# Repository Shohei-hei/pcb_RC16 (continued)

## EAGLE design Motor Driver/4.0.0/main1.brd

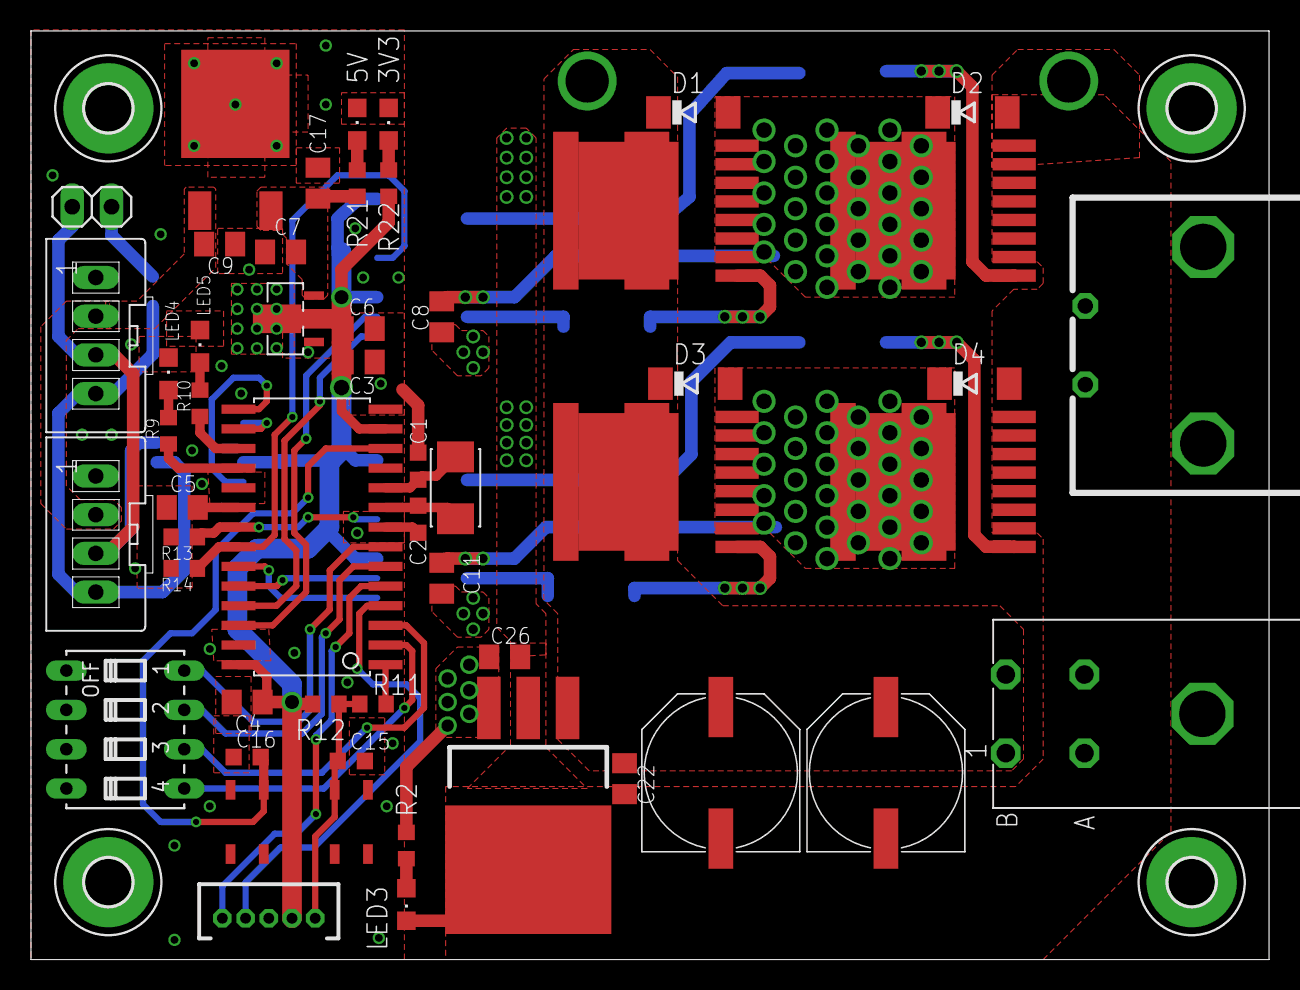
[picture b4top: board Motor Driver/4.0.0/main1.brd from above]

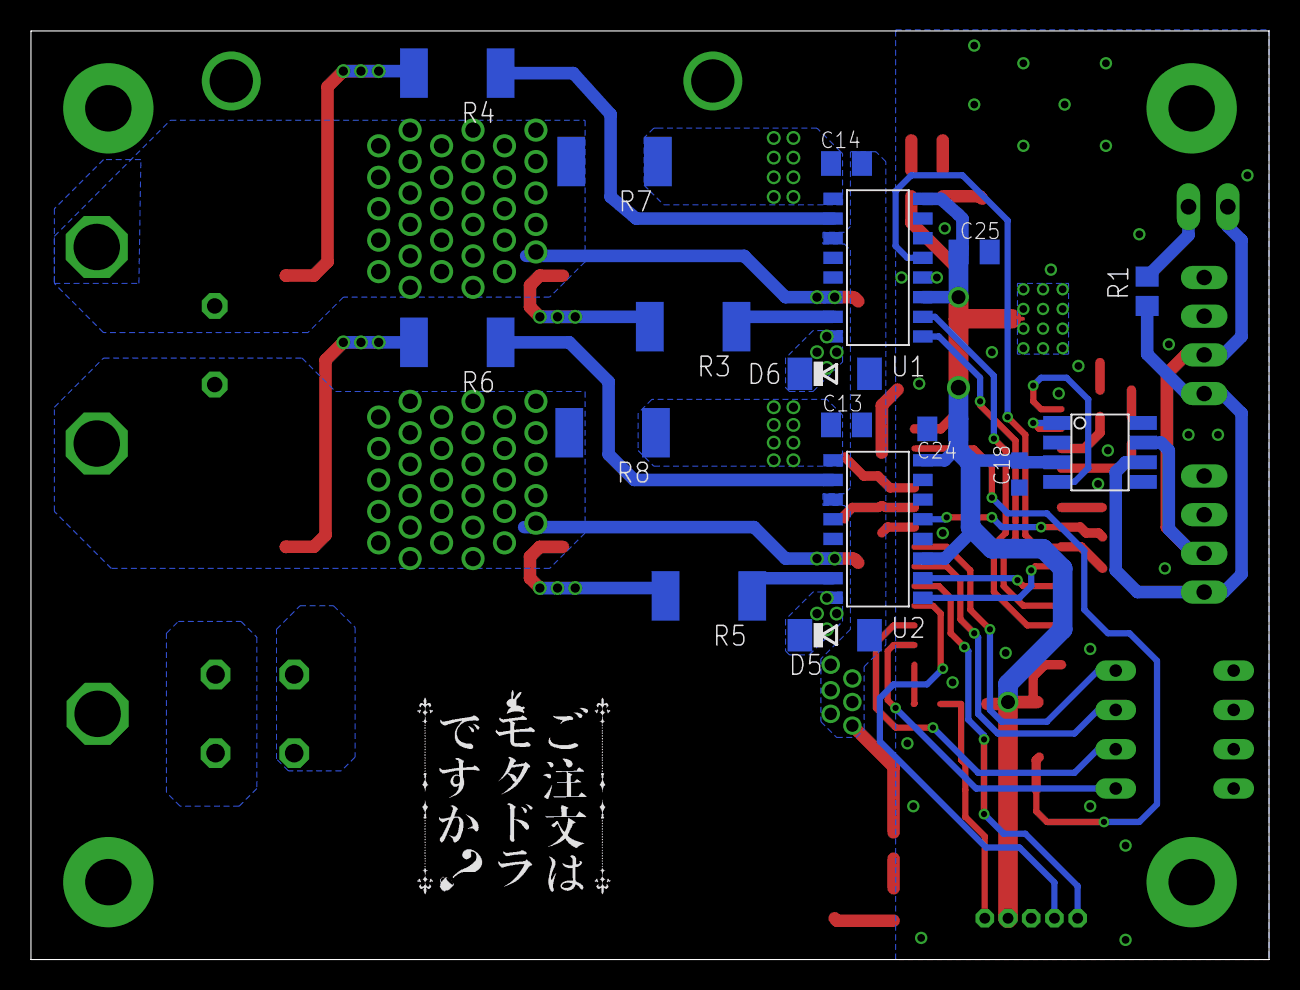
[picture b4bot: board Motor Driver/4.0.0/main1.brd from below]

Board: 2 copper layers, 80.0 x 60.0 mm, 75 parts (18 on the bottom side), 49 nets.

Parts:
3V3, 5V: CHIPLED_0805
C1, C2: 22p; C0603K
C3, C4, C13, C14, C24, C25: 0.1u; C0805K
C5, C6, C7, C8, C9, C11, C17, C22, C26: 4.7u; C0805K
C12, C21: PANASONIC_G
C15, C16, C18: 0.1u; C0603K
CN2, CN3: XA04-T; XA04
D1, D2, D3, D4: SBD; SOD106-R
D5, D6: SOD106-R
H5, H6, H7, H8: MOUNT-PAD-ROUND3.0; 3,0-PAD
IC1: DSPIC33FJ32MC302/64MC202/64MC802/128MC202/128MC802; SOIC28
IC2: REGULATERNJM2845DL1; TO-252-2
IC4: REGULATERAZ1117CR; SOT89
JP3: 1X02
LED3, LED4, LED5: CHIPLED_0805
MC7812BDTRKGOSCT-ND1: REGULATERMIC2940A-5.0WU; TO-263-3
Q2: CRYSTALNX5032GA; NX5032GA
R1: 120; R0805
R2, R12: 1k; R0603
R3, R4, R5, R6: 33; R2512
R7, R8: 470; R2512
R9, R10, R13, R14, R21, R22: 510; R0603
R11: 330; R0603
S2: DIP04S
SW1, SW2: SWITCH_4PALPS; SKRP
U1, U2: SOIC16_N
U$1: CN-D3500D04; D-3500D04
U$2, U$3, U$4, U$5: FET_NCHFDBL0065N40; MO-299A
U$6: MAX3051; SOIC8
U$7: WRITE_FOR_PICT; ZH05
U$8: LOGOGOCHIUSA-14MM; LOGO006
U$9: CN-D3200S02; D-3200S02-S

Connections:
0V: C12.-, C13.2, C14.2, C21.-, C22.2, C26.2, D2.A, D4.A, LED3.C, MC7812BDTRKGOSCT-ND1.2, MC7812BDTRKGOSCT-ND1.4, R7.1, R8.1, U1.P$9, U2.P$9, U$1.01A, U$1.02A, U$3.2, U$3.3, U$3.4, U$3.5, U$3.6, U$3.7, U$3.8, U$5.2, U$5.3, U$5.4, U$5.5, U$5.6, U$5.7, U$5.8
3.3V: C3.1, C4.1, C6.2, C18.2, C24.1, C25.1, IC1.13, IC1.28, IC4.2, IC4.P, R12.2, R22.1, U1.P$3, U1.P$8, U2.P$3, U2.P$8, U$6.3, U$7.2
+5V: C7.2, C17.2, IC2.3, IC4.3, R21.1
+10V: C9.2, CN2.PIN2, CN3.PIN2, IC2.1
BOOTA: C8.1, D6.C, U1.P$16
BOOTB: C11.1, D5.C, U2.P$16
CANH: CN2.PIN3, CN3.PIN3, JP3.2, U$6.7
CANL: CN2.PIN4, CN3.PIN4, R1.1, U$6.6
CRXD: IC1.15, U$6.4
CTXD: IC1.16, U$6.1
DGND: 3V3.C, 5V.C, C1.1, C2.1, C3.2, C4.2, C5.2, C6.1, C7.1, C9.1, C15.2, C16.1, C17.1, C18.1, C24.2, C25.2, CN2.PIN1, CN3.PIN1, IC1.8, IC1.19, IC1.27, IC2.2, IC4.1, LED4.C, LED5.C, R13.2, R14.2, S2.1, S2.2, S2.3, S2.4, SW1.1, SW1.2, SW2.3, SW2.4, U1.P$4, U2.P$4, U$6.2, U$6.5, U$6.8, U$7.3
DIS_A: IC1.22, R14.1, U1.P$5
DIS_B: IC1.21, R13.1, U2.P$5
HA: R3.1, U1.P$15
HB: R5.1, U2.P$15
LA: R4.1, U1.P$10
LB: R6.1, U2.P$10
LED0: IC1.18, R9.1
LED1: IC1.17, R10.1
MCLR: C15.1, R11.1, R12.1, SW1.3, U$7.1
unnamed: C2.2, IC1.9, Q2.2
unnamed: C1.2, IC1.10, Q2.1
unnamed: C5.1, IC1.20
unnamed: JP3.1, R1.2
unnamed: LED3.A, R2.1
unnamed: LED4.A, R9.2
unnamed: LED5.A, R10.2
unnamed: R3.2, U$2.1
unnamed: R4.2, U$3.1
unnamed: R6.2, U$5.1
unnamed: R5.2, U$4.1
unnamed: IC1.1, R11.2
unnamed: 5V.A, R21.2
unnamed: 3V3.A, R22.2
OUT+: C8.2, D1.A, D2.C, R7.2, U1.P$14, U$2.2, U$2.3, U$2.4, U$2.5, U$2.6, U$2.7, U$2.8, U$3.PAD1, U$3.PAD2, U$3.PAD3, U$3.PAD4, U$9.2, U$9.P$2
OUT-: C11.2, D3.A, D4.C, R8.2, U2.P$14, U$4.2, U$4.3, U$4.4, U$4.5, U$4.6, U$4.7, U$4.8, U$5.PAD1, U$5.PAD2, U$5.PAD3, U$5.PAD4, U$9.1, U$9.P$1
PGEC: IC1.5, U$7.5
PGED: IC1.4, U$7.4
PWMHA: IC1.25, U1.P$1
PWMHB: IC1.23, U2.P$1
PWMLA: IC1.26, U1.P$2
PWMLB: IC1.24, U2.P$2
SW: C16.2, IC1.12, SW2.1
SW0: IC1.7, S2.8
SW1: IC1.6, S2.7
SW2: IC1.3, S2.6
SW3: IC1.2, S2.5
VCC_1: C13.1, C14.1, C26.1, D5.A, D6.A, MC7812BDTRKGOSCT-ND1.3, R2.2, U1.P$11, U2.P$11
VDD: C12.+, C21.+, C22.1, D1.C, D3.C, MC7812BDTRKGOSCT-ND1.1, U$1.01B, U$1.02B, U$2.PAD1, U$2.PAD2, U$2.PAD3, U$2.PAD4, U$4.PAD1, U$4.PAD2, U$4.PAD3, U$4.PAD4

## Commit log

2016-03-07 eco new
2016-07-20 nya-n
